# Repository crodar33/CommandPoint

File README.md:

# Code and shecme for control inverter
Scheme based on ESP8266 for pool data from BSM of the battery with **daly smart bms**
and provide battery data to **SOFAR HYBRID** inverter **HYD6000-ES**

They not compatible to each to other, so I need to make middle man for it work together.

In current implementation it can:

  * pull data from battery by RS485, UART
  * put data to the inverter by CAN and inner inverter protocol
  * show battery state by HTTP
  * show battery errors

Used ESP8266, MCP2515, MAX485 and nodeMCU, code writed on LUA
Build nodemcu with **I2C_MASTER_GPIO16_ENABLE** and without **I2C_MASTER_OLD_VERSION**
LUA_USE_MODULES_SOFTUART
LUA_USE_MODULES_STRUCT
LUA_USE_MODULES_U8G2

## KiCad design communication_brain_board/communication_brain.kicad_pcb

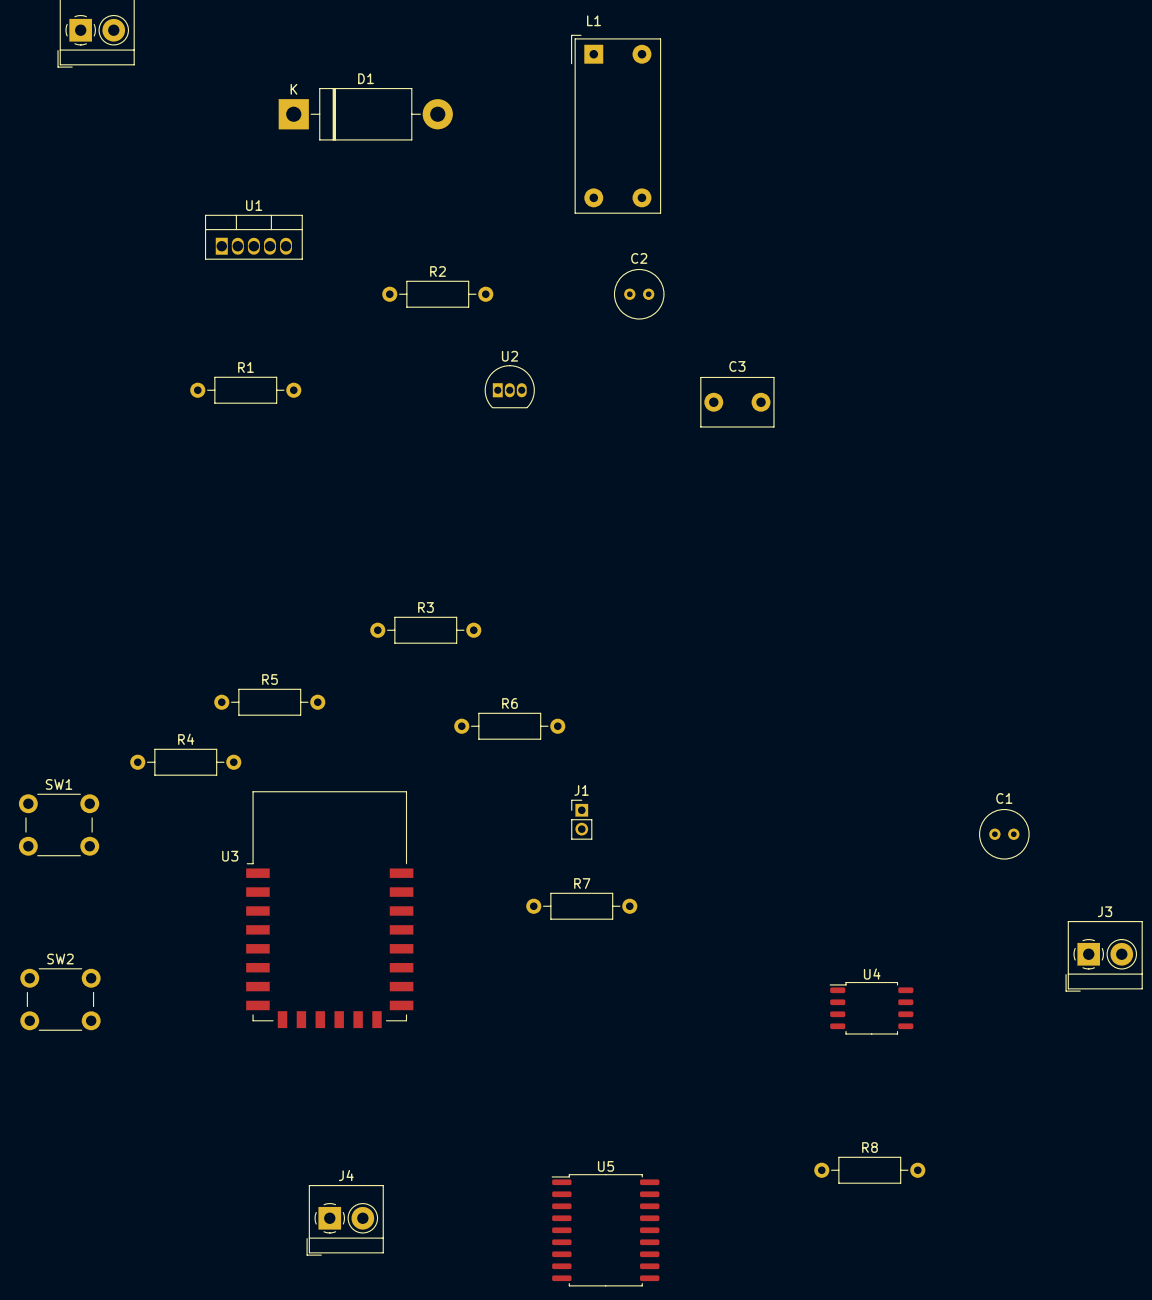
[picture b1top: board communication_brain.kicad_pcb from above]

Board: 2 copper layers, 24 parts (0 on the bottom side), 23 nets, no tracks yet.

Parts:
C1: 100mF; C_Radial_D5.0mm_H5.0mm_P2.00mm
C2: 1000mF; C_Radial_D5.0mm_H5.0mm_P2.00mm
C3: 0.1mF; C_Disc_D7.5mm_W5.0mm_P5.00mm
D1: 1N5822; D_DO-201AD_P15.24mm_Horizontal
J1: UART; PinHeader_1x02_P2.00mm_Vertical
J2: Batt; TerminalBlock_4Ucon_1x02_P3.50mm_Horizontal
J3: RS485; TerminalBlock_4Ucon_1x02_P3.50mm_Horizontal
J4: CAN; TerminalBlock_4Ucon_1x02_P3.50mm_Horizontal
L1: 100mH; Choke_Schaffner_RN202-04-8.8x18.2mm
R1: 5.6k; R_Axial_DIN0207_L6.3mm_D2.5mm_P10.16mm_Horizontal
R2: 1.8k; R_Axial_DIN0207_L6.3mm_D2.5mm_P10.16mm_Horizontal
R3, R4, R5, R6, R7, R8: 10k; R_Axial_DIN0207_L6.3mm_D2.5mm_P10.16mm_Horizontal
SW1: Reset; SW_PUSH_6mm_H5mm
SW2: Programm; SW_PUSH_6mm_H5mm
U1: LM2576HVT-ADJ; TO-220-5_Vertical
U2: L78L33_TO92; TO-92_Inline
U3: ESP-12E
U4: MAX485E; SOIC-8_5.23x5.23mm_P1.27mm
U5: MCP2515-xSO; SOIC-18W_7.5x11.6mm_P1.27mm

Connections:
+3V3: C3.1, R3.1, R4.1, R5.1, R6.1, U2.1, U3.8, U4.8, U5.9, U5.18
+5V: C2.1, L1.2, R2.1, U2.3
+BATT: C1.1, J2.2, U1.1
-BATT: C1.2, C2.2, C3.2, D1.2, J2.1, R1.2, R7.2, R8.2, SW1.1, SW1.2, SW2.1, SW2.2, U1.3, U1.5, U2.2, U3.15, U4.5
/CS: U3.9, U5.16
/RXD: J1.1, U3.21
/SCK: U3.14, U5.13
/SI: U3.13, U5.14
/SO: U3.10, U5.15
/TXD: J1.2, U3.22
unnamed: D1.1, L1.1, U1.2
unnamed: J3.1, U4.7
unnamed: J3.2, U4.6
unnamed: J4.1, U5.2
unnamed: J4.2, U5.1
unnamed: R1.1, R2.2, U1.4
unnamed: R3.2, U3.3
unnamed: R4.2, U3.1
unnamed: R5.2, U3.18
unnamed: R6.2, U3.17, U4.1
unnamed: R7.1, U3.16
unnamed: R8.1, U3.6, U4.2, U4.3
unnamed: U3.7, U4.4

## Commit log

2021-03-23 initial commit of all stuff
2021-03-29 optimizations and changes: - httpMuted flag for stop internals protocols - http post parser - changes in spi logic
2021-03-29 moved rs485 files removed WIFI config
2021-03-29 compile for rs485
2021-04-03 Web optimistations
2021-04-03 scheme added in git
2021-04-03 readme added and license
2021-04-05 fixed scheme
2021-05-03 Schema update, little adjustments
2021-05-04 show temperature on state page, fixed battery state status show, added turbo charge - for "kicking" battery if it is desynchronizated
2021-09-20 reworked battarey communication for use daly smart bms
2021-09-21 update http server
2021-09-21 update CAN information and init file
2021-09-21 update shceme
2021-09-22 update of readmy
2021-09-26 restart if no wifi
2021-09-26 added support of display and little changes
2021-09-27 added CRC
2021-09-27 fixed current dispaly (we can't % negative values ...)
2021-09-27 fixed inverter communication
2021-09-27 more full details
2021-10-07 little optimizations
2021-11-24 added: - tcp modbus communication to battery - udb proadcast of battery stait - prepare for RS485 communication with invertor - updated readmy (modules needed for build) - stability
2022-11-28 added check of daly errors, added charge request in cell imbalance case
2022-12-03 added mod for longer charge (balancing)
2023-07-05 some fixes
2024-02-14 redused brightnes
2024-03-13 reworked to use Jiкоng bms, reworked work with spi-can library, reworked http server, smal fixes
2024-03-13 web module fixes
2024-04-20 optimizations, fixes and other
2024-04-20 fixed bug with discharge limitation
2024-04-22 updated bms logc, updated web information and store
2024-04-24 removed test code
2025-05-04 reworked charge profile: now you can set max charge current on force charge + current control on dis-balanced charge
2026-06-23 possibility for discharge battery for fine calibration, small fixes
